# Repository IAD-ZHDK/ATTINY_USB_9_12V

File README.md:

# ATTINY_USB_9_12V
 A QC3 9 or 12 volt supply based on Attiny 45

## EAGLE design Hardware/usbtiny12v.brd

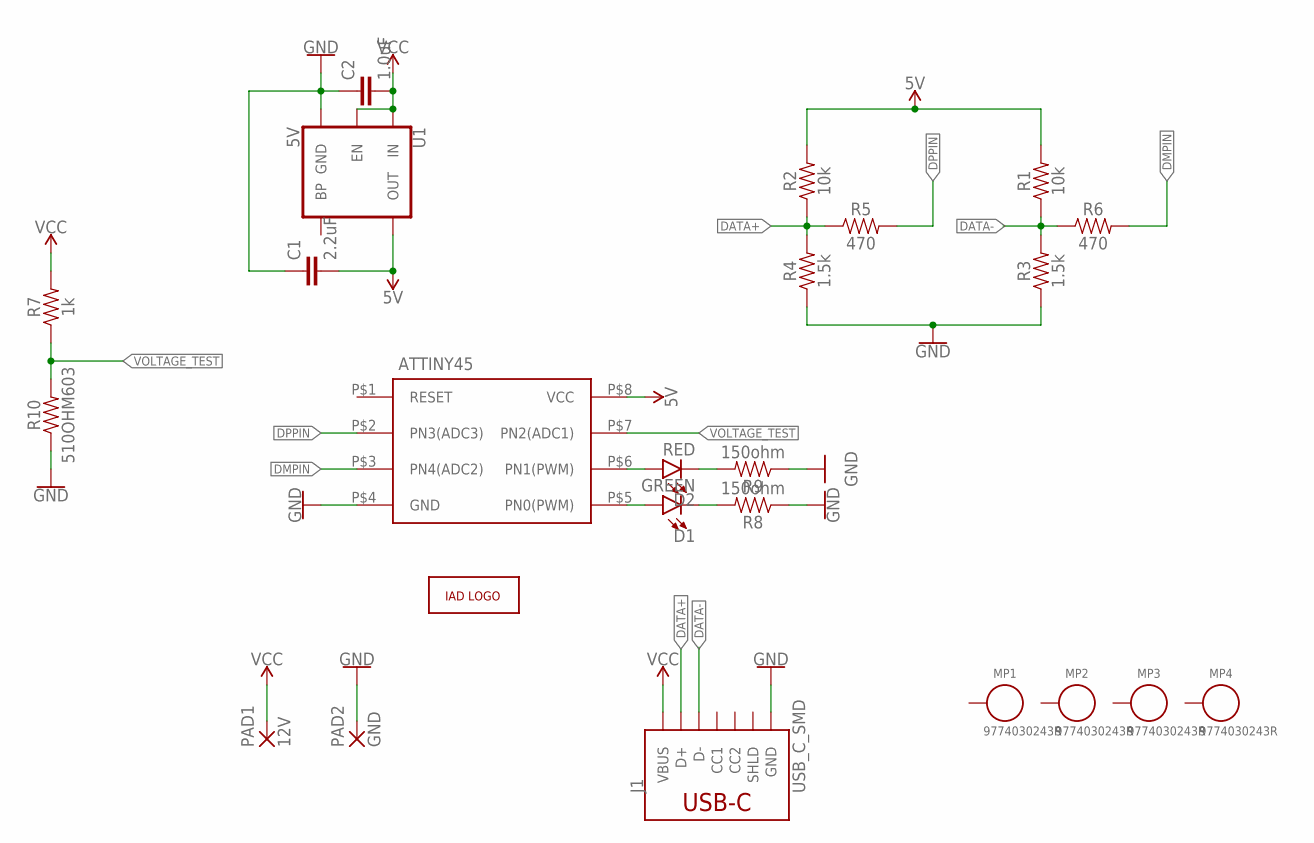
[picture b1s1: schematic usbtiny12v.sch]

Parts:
C1: 2.2uF; 1206
C2: 1.0uF; 1206
D1: GREEN; LED-0603
D2: RED; LED-0603
J1: USB_C_SMD
MP1, MP2, MP3, MP4: 9774030243R; WA-SMSI_9774030243
PAD1: 12V; SMD2,54-5,08
PAD2: GND; SMD2,54-5,08
R1, R2: 10k; 0603
R3, R4: 1.5k; 0603
R5, R6: 470; 0603
R7: 1k; 0603
R8, R9: 150ohm; 0603
R10: 510OHM603; 0603
U1: 5V; SOT23-5
U2: ATTINY45GULLWINGDIP; GULLWING_SMD
U$6: ZHDK_LOGO_METAL; ZHDK_LOGO

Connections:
5V: C1.2, R1.2, R2.2, U1.5 (OUT), U2.P$8 (VCC)
DATA+: J1.A6 (D+), J1.B6 (D+), R2.1, R4.2, R5.1
DATA-: J1.A7 (D-), J1.B7 (D-), R1.1, R3.2, R6.1
DMPIN: R6.2, U2.P$3 (PN4(ADC2))
DPPIN: R5.2, U2.P$2 (PN3(ADC3))
GND: C1.1, C2.1, J1.GND, J1.GND2 (GND), PAD2.1, R3.1, R4.1, R8.1, R9.1, R10.1, U1.2 (GND), U2.P$4 (GND)
unnamed: D1.C, R8.2
unnamed: D2.A, U2.P$6 (PN1(PWM))
unnamed: D2.C, R9.2
unnamed: D1.A, U2.P$5 (PN0(PWM))
VCC: C2.2, J1.VBUS1 (VBUS), J1.VBUS2 (VBUS), PAD1.1, R7.2, U1.1 (IN), U1.3 (EN)
VOLTAGE_TEST: R7.1, R10.2, U2.P$7 (PN2(ADC1))

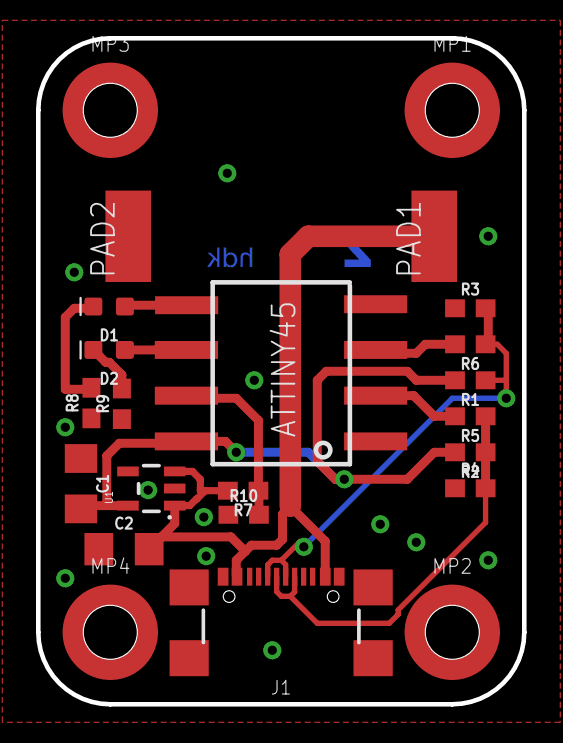
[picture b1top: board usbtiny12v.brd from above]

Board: 2 copper layers, 27.0 x 37.0 mm, 24 parts (1 on the bottom side), 12 nets.

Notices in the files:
parts and their libraries:
SparkFun-Resistors: Licensing: Creative Commons ShareAlike 4.0 International - https://creativecommons.org/licenses/by-sa/4.0
Wurth_Assembly_WA-SMSI: Copyright: Würth Elektronik
